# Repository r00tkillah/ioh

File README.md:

ioh
===

Internet of hats

see our home page https://r00tkillah.github.io/ioh
see the wiki https://github.com/r00tkillah/ioh/wiki

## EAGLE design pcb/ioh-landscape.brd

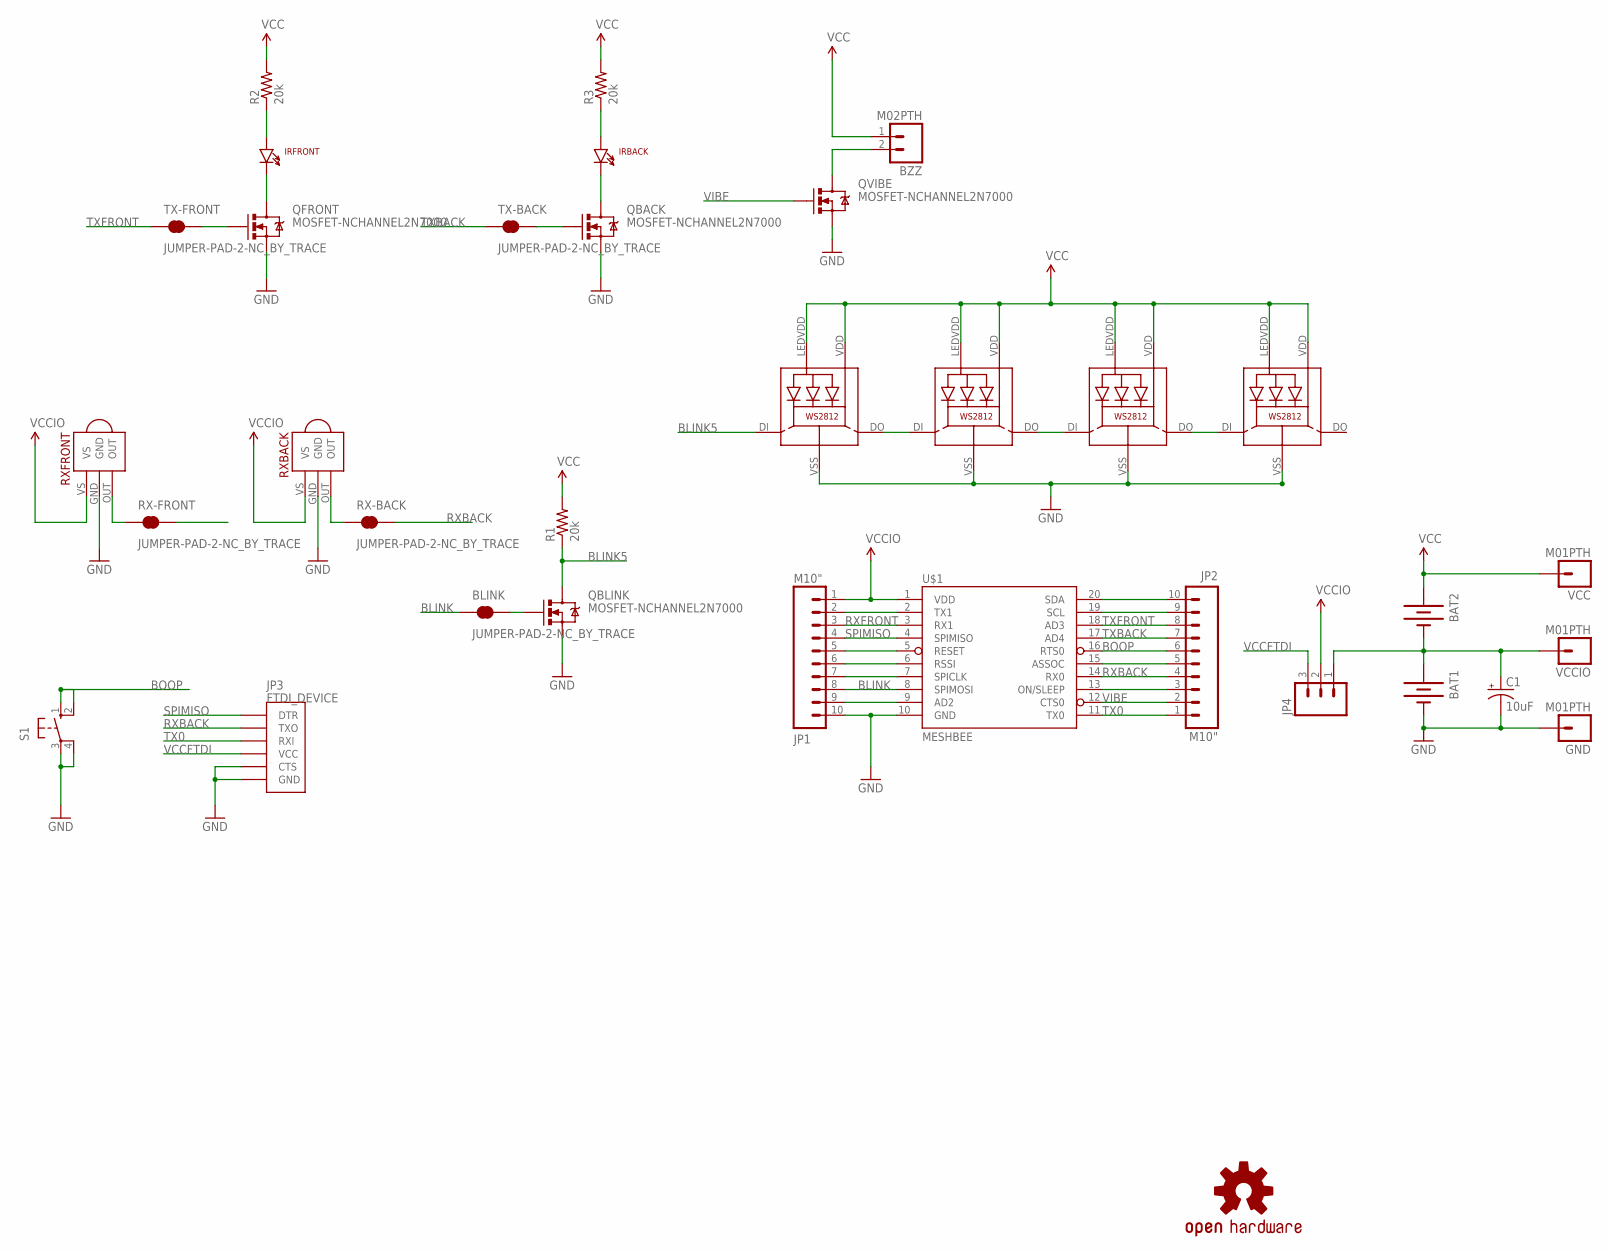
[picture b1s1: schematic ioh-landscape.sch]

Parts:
BAT1, BAT2: BATTERY20PTH; BATTCOM_20MM_PTH
BLINK: JUMPER-PAD-2-NC_BY_TRACE; PAD-JUMPER-2-NC_BY_TRACE_YES_SILK
BZZ: M02PTH; 1X02
C1: 10uF; CPOL-RADIAL-10UF-25V-KIT
GND: M01PTH; 1X01
IRBACK: LTE-302
IRFRONT: LTE-302
JP1, JP2: M10"; 1X10
JP3: FTDI_DEVICE; FTDI_DEVICE_SIDE
JP4: M03LOCK; 1X03_LOCK
LED2, LED3, LED4, LED5: WS2812
LOGO1: OSHW-LOGOS; OSHW-LOGO-S
QBACK: MOSFET-NCHANNEL2N7000; TO-92
QBLINK: MOSFET-NCHANNEL2N7000; TO-92
QFRONT: MOSFET-NCHANNEL2N7000; TO-92
QVIBE: MOSFET-NCHANNEL2N7000; TO-92
R1, R2, R3: 20k; AXIAL-0.4
RX-BACK: JUMPER-PAD-2-NC_BY_TRACE; PAD-JUMPER-2-NC_BY_TRACE_YES_SILK
RX-FRONT: JUMPER-PAD-2-NC_BY_TRACE; PAD-JUMPER-2-NC_BY_TRACE_YES_SILK
RXBACK: TSOP2438
RXFRONT: TSOP2438
S1: 40-XX; B3F-40XX
TX-BACK: JUMPER-PAD-2-NC_BY_TRACE; PAD-JUMPER-2-NC_BY_TRACE_YES_SILK
TX-FRONT: JUMPER-PAD-2-NC_BY_TRACE; PAD-JUMPER-2-NC_BY_TRACE_YES_SILK
U$1: MESHBEE
VCC: M01PTH; 1X01
VCCIO: M01PTH; 1X01

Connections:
BLINK: BLINK.1, JP1.8, U$1.8 (SPIMOSI)
BLINK5: LED2.DI, QBLINK.3 (D), R1.P$1 (1)
BOOP: JP2.6, S1.1 (S), S1.2 (S1), U$1.16 (RTS0)
GND: BAT1.2 (-), C1.2 (-), GND.1, JP1.10, JP3.P$5 (CTS), JP3.P$6 (GND), LED2.VSS (GND), LED3.VSS (GND), LED4.VSS (GND), LED5.VSS (GND), QBACK.1 (S), QBLINK.1 (S), QFRONT.1 (S), QVIBE.1 (S), RXBACK.GND, RXFRONT.GND, S1.3, S1.4 (P1), U$1.10 (GND)
unnamed: LED2.DO, LED3.DI
unnamed: LED3.DO, LED4.DI
unnamed: LED4.DO, LED5.DI
unnamed: IRFRONT.A, R2.P$1 (1)
unnamed: JP1.2, U$1.2 (TX1)
unnamed: BLINK.2, QBLINK.2 (G)
unnamed: JP1.5, U$1.5 (RESET)
unnamed: JP1.6, U$1.6 (RSSI)
unnamed: JP1.7, U$1.7 (SPICLK)
unnamed: IRFRONT.C, QFRONT.3 (D)
unnamed: JP1.9, U$1.9 (AD2)
unnamed: BZZ.2, QVIBE.3 (D)
unnamed: BAT1.1 (+), BAT2.2 (-), C1.1 (+), JP4.1, VCCIO.1
unnamed: RX-BACK.1, RXBACK.OUT
unnamed: JP2.3, U$1.13 (ON/SLEEP)
unnamed: RX-FRONT.1, RXFRONT.OUT
unnamed: JP2.5, U$1.15 (ASSOC)
unnamed: QFRONT.2 (G), TX-FRONT.2
unnamed: QBACK.2 (G), TX-BACK.2
unnamed: JP2.9, U$1.19 (SCL)
unnamed: JP2.10, U$1.20 (SDA)
unnamed: IRBACK.A, R3.P$1 (1)
unnamed: IRBACK.C, QBACK.3 (D)
RXBACK: JP2.4, JP3.P$2 (TXO), RX-BACK.2, U$1.14 (RX0)
RXFRONT: JP1.3, RX-FRONT.2, U$1.3 (RX1)
SPIMISO: JP1.4, JP3.P$1 (DTR), U$1.4 (SPIMISO)
TX0: JP2.1, JP3.P$3 (RXI), U$1.11 (TX0)
TXBACK: JP2.7, TX-BACK.1, U$1.17 (AD4)
TXFRONT: JP2.8, TX-FRONT.1, U$1.18 (AD3)
VCC: BAT2.1 (+), BZZ.1, LED2.LEDVDD, LED2.VDD, LED3.LEDVDD, LED3.VDD, LED4.LEDVDD, LED4.VDD, LED5.LEDVDD, LED5.VDD, R1.P$2 (2), R2.P$2 (2), R3.P$2 (2), VCC.1
VCCFTDI: JP3.P$4 (VCC), JP4.3
VCCIO: JP1.1, JP4.2, RXBACK.VS, RXFRONT.VS, U$1.1 (VDD)
VIBE: JP2.2, QVIBE.2 (G), U$1.12 (CTS0)

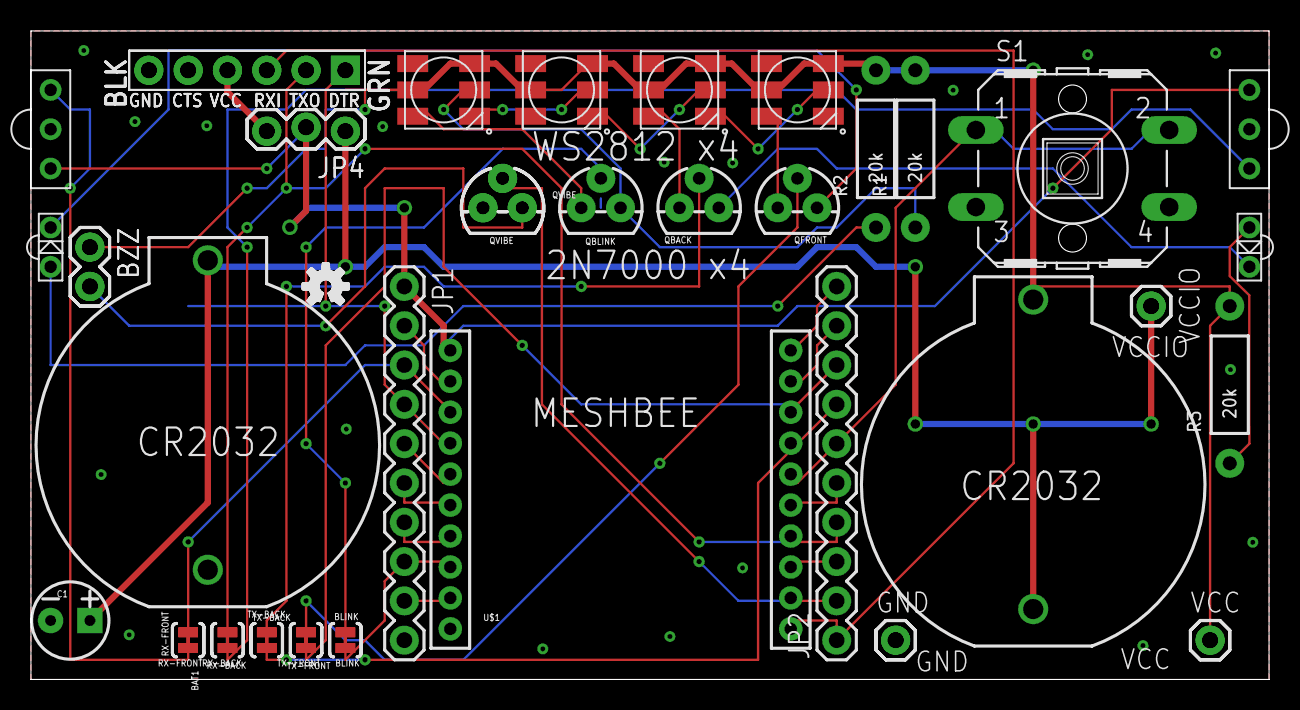
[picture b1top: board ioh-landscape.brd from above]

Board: 2 copper layers, 80.0 x 41.9 mm, 35 parts (0 on the bottom side), 37 nets.

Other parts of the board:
U$2: BSIDES

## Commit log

2014-08-18 Create README.md
    something is better that nothing. most of the time
2014-08-19 Create gh-pages branch via GitHub
2014-09-12 Beginings of board in eagle
2014-09-12 add adafruit eagle library
2014-09-12 add sparkfun eagle library
2014-09-12 add junctions to shut erc up
2014-09-12 add front/back tx
2014-09-13 tsop library addition; placement
2014-09-13 vibe placement; update todo; caps
2014-09-13 add switch
2014-09-13 actually connect things
2014-09-13 some names
2014-09-13 power test points
2014-09-13 solder jumpers
2014-09-14 ftdi connector
2014-09-14 add labels; connect boop
2014-09-14 moved stuff around; put it in a box
2014-09-14 remove the .brd file since it is out of sync
2014-09-14 bsides logo part
2014-09-14 place bsides logo
2014-09-14 move to origin
2014-09-16 remove the text
2014-09-16 portrait board
2014-09-16 playing around with layouts
2014-09-17 updating due to oshpark drc
2014-09-17 routed
2014-09-17 some smashing and moving of labels
2014-09-17 most power routed
2014-09-17 autorouted
2014-09-17 removed via on top of via issue
2014-09-17 smashing and silk
2014-09-17 more smashing and silk
2014-09-17 update bsides package
2014-09-17 place new bsides logo
2014-09-18 switch from cts->spimiso to dtr->spimiso
2014-09-19 add some ws2812 twiddling code
2014-09-19 Invert the output and disable the interrupt
    The transistor inverts our output and we don't use the interrupt
2014-09-20 added top ground plane and several ground vias. adjusted a few traces to pass drc. added cam file for generating gerbers, plus generated gerbers. added top/bottom preview images from gerbv.
2014-09-20 fixing top image to lower quality but more accurate rendering
2014-09-20 adding some documentation text to front and back
2014-09-21 import JN-AN-1190 to node/
    A starting point
2014-09-21 Modify DeviceDio Makefile to make it build
    I don't know why the shell variables don't work for me, but
    hard-coding the makefile does. ;)
2014-09-21 The invert bit is for the clock polarity, not data
    Remove stupid on my part. Must invert data, not clock.
2014-09-22 add schematic pdf
2014-09-23 Add hat MIB
    Right now, it does nothing and is a blatent copy-pasta of DioConfig.
    It does, however, compile.
2014-09-23 Tidy things up with a git-ignore for node
2014-09-24 DRY up cut and paste job
2014-09-25 remove this stuff since we sent it to ioh-node

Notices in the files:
parts and their libraries:
SparkFun-Electromechanical: Licensing: Creative Commons ShareAlike 4.0 International - https://creativecommons.org/licenses/by-sa/4.0
